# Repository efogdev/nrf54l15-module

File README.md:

## Codename "Chinchilla"

### ❗️ DO NOT BUILD ❗️
### ❗️ The design has a critical issue ❗️

## Features

1. Full IO set: all the GPIO and programming pins are present
2. Compact design: the board is 16.4x25.3 mm with ≈4.8 mm of total height
3. Ultra efficient: featuring TLV62569 with ≥92% efficiency at (almost) any load
4. 1V8 pin can be used as both input (if VIN not connected) and output (up to 1.5A)
5. 4 programmable LEDs (200 µA) that can be isolated to free the pins
6. On-board "reset" switch and an additional general purpose button (High/High-Z)
7. Impedance of (almost) all traces is close to 50Ω
8. Board-to-board connector with programming, power and GPIO pins 

## Stackup

JLC06121H-3313

## Dimensions

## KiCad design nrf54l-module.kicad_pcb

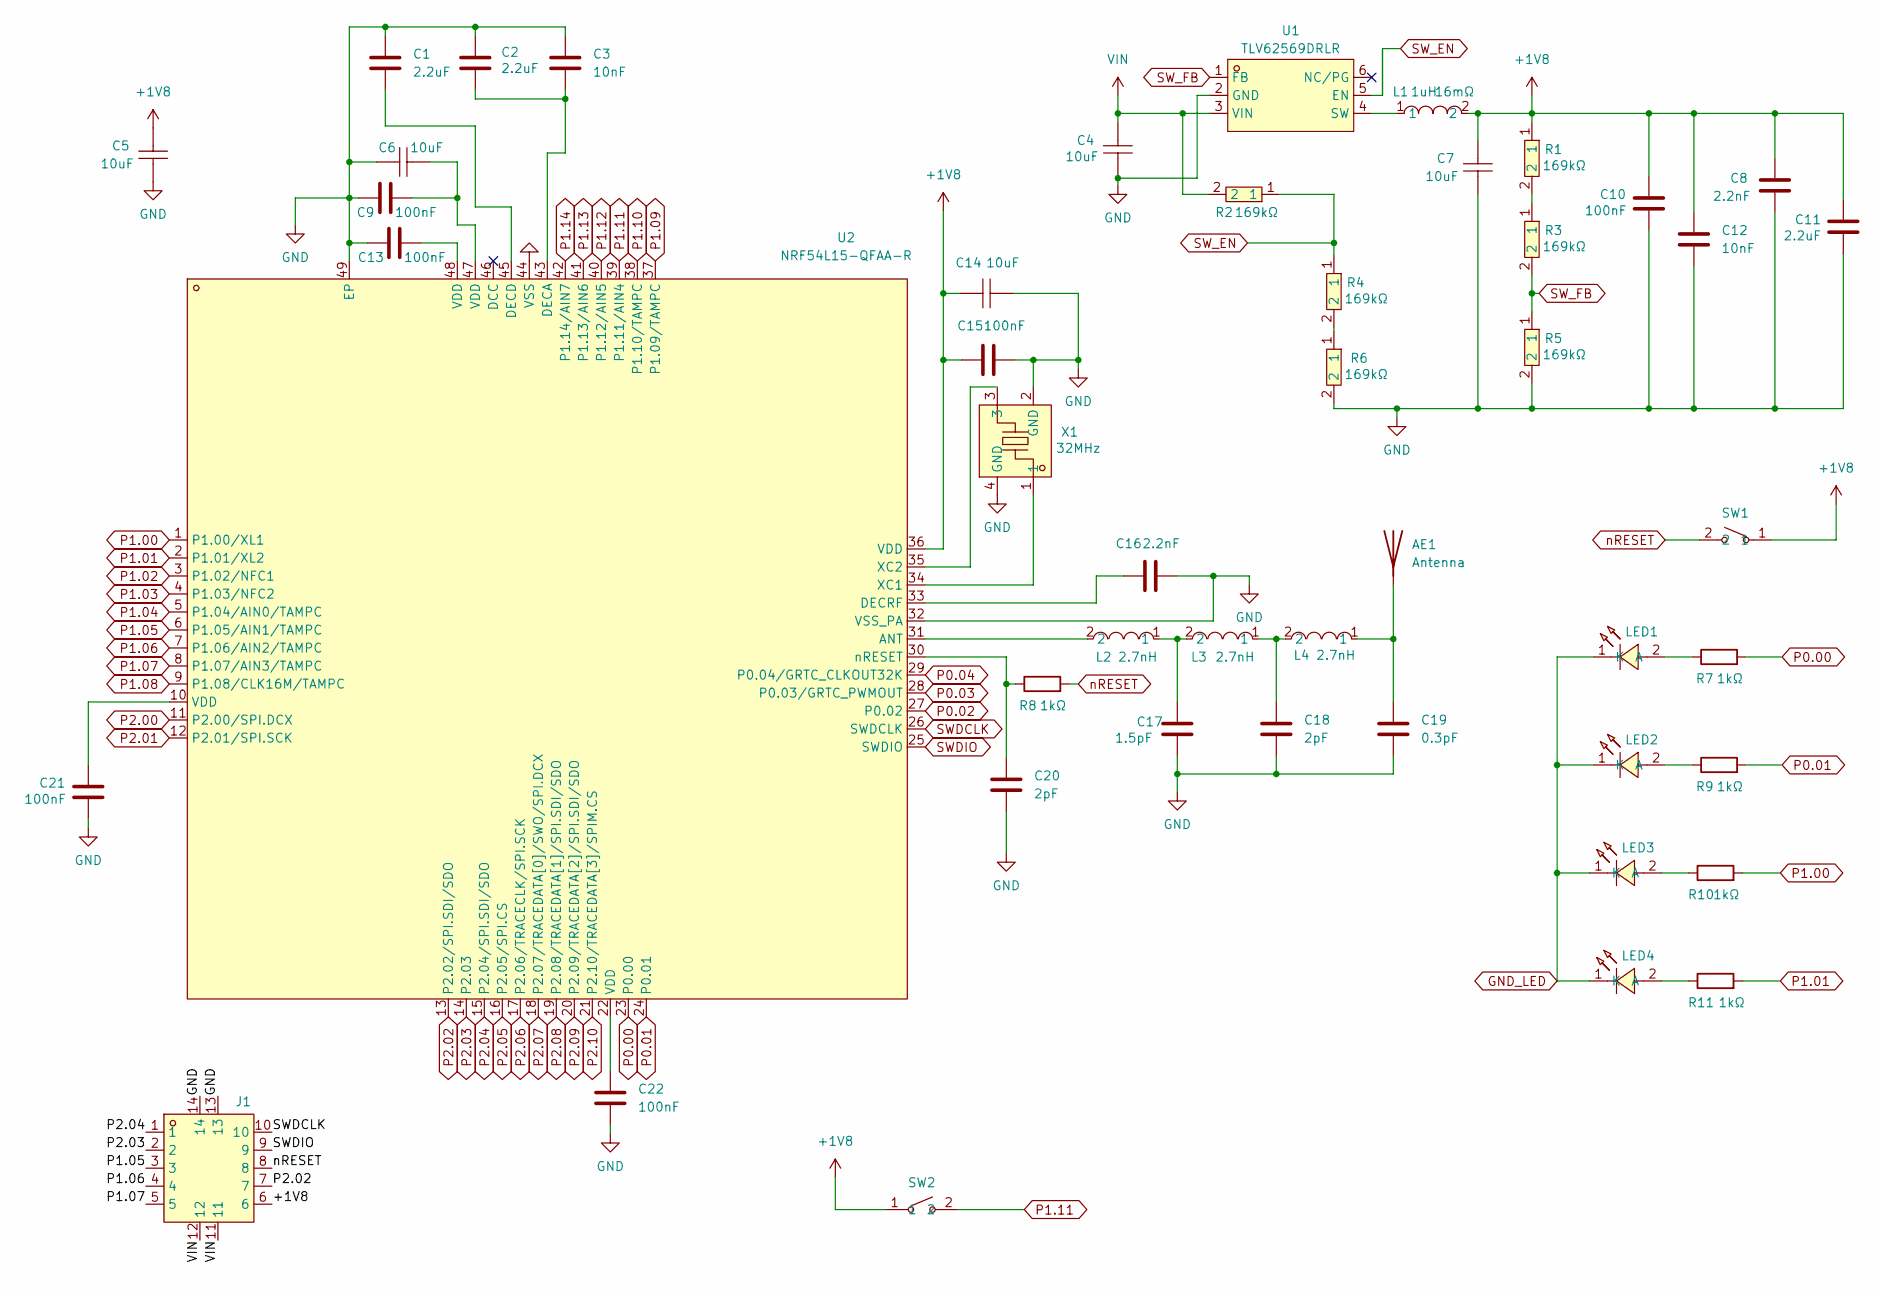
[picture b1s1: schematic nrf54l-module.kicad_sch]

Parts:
AE1: Antenna; Texas_SWRA117D_2.4GHz_Left
C1, C2, C11: 2.2uF; C_0201_0603Metric; LCSC Part C76933
C3, C12: 10nF; C_0201_0603Metric; LCSC Part C76941
C4, C5, C6, C7, C14: 10uF; C0402; LCSC Part C76991
C8, C16: 2.2nF; C_0201_0603Metric; LCSC Part C97860
C9, C10, C13, C15, C21, C22: 100nF; C_0201_0603Metric; LCSC Part C668346
C17: 1.5pF; C_0201_0603Metric; LCSC Part C88913
C18, C20: 2pF; C_0201_0603Metric; LCSC Part C426046
C19: 0.3pF; C_0201_0603Metric; LCSC Part C76927
J1: BM28B0.6-10DS/2-0.35V(51); CONN-SMD_BM28B0.6-10DS-2-0.35V-51; LCSC Part C424563
L1: 1uH; L1008; LCSC Part C22400405
L2, L3, L4: MLG0603P2N7CT000; L0201; LCSC Part C76752
LED1, LED2, LED3, LED4: TZ-P2-0402RTIA1-0.45T; LED0402-RD_RED; LCSC Part C779449
R1, R2, R3, R4, R5, R6: RC0402FR-07160KL; R_0201_0603Metric; LCSC Part C166333
R7, R8, R9, R10, R11: 1kΩ; R_0201_0603Metric; LCSC Part C270365
SW1, SW2: KEY-SMD_B3U-1000PM; LCSC Part C231329
U1: TLV62569DRLR; SOT-563_L1.6-W1.2-P0.50-LS1.6-BL; LCSC Part C163217
U2: NRF54L15-QFAA-R; QFN-48_L6.0-W6.0-P0.40-TL-EP4.6; LCSC Part C42458750
X1: XL7EL89CKI-111YLC-32M; CRYSTAL-SMD_4P-L2.0-W1.6-BL; LCSC Part C2965582

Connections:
+1V8: C5.1, C7.1, C8.2, C10.2, C11.2, C12.1, C14.1, C15.1, J1.6, L1.2, R1.1, SW1.1, SW2.1, U2.36 (VDD)
GND: AE1.2, C1.1, C2.1, C3.1, C4.1, C5.2, C6.1, C7.2, C8.1, C9.1, C10.1, C11.1, C12.2, C13.2, C14.2, C15.2, C16.2, C17.2, C18.2, C19.2, C20.2, C21.1, C22.2, J1.13, J1.14, R5.2, R6.2, U1.2 (GND), U2.32 (VSS_PA), U2.44 (VSS), U2.49 (EP), X1.2 (GND), X1.4 (GND)
GND_LED: LED1.1 (K), LED2.1 (K), LED3.1 (K), LED4.1 (K)
unnamed: AE1.1 (A), C19.1, L4.1
unnamed: C6.2, C9.2, U2.47 (VDD)
unnamed: C13.1, U2.48 (VDD)
unnamed: C17.1, L2.1, L3.2
unnamed: C18.1, L3.1, L4.2
unnamed: C21.2, U2.10 (VDD)
unnamed: C22.1, U2.22 (VDD)
unnamed: LED1.2 (A), R7.1
unnamed: LED2.2 (A), R9.1
unnamed: LED3.2 (A), R10.1
unnamed: LED4.2 (A), R11.1
unnamed: R1.2, R3.1
unnamed: R4.2, R6.1
unnamed: L1.1, U1.4 (SW)
unnamed: L2.2, U2.31 (ANT)
unnamed: C2.2, C3.2, U2.43 (DECA)
unnamed: C1.2, U2.45 (DECD)
unnamed: C16.1, U2.33 (DECRF)
unnamed: U2.34 (XC1), X1.1
unnamed: U2.35 (XC2), X1.3
unnamed: C20.1, R8.1, U2.30 (nRESET)
P0.00: R7.2, U2.23 (P0.00)
P0.01: R9.2, U2.24 (P0.01)
P0.02: U2.27 (P0.02)
P0.03: U2.28 (P0.03/GRTC_PWMOUT)
P0.04: U2.29 (P0.04/GRTC_CLKOUT32K)
P1.00: R10.2, U2.1 (P1.00/XL1)
P1.01: R11.2, U2.2 (P1.01/XL2)
P1.02: U2.3 (P1.02/NFC1)
P1.03: U2.4 (P1.03/NFC2)
P1.04: U2.5 (P1.04/AIN0/TAMPC)
P1.05: J1.3, U2.6 (P1.05/AIN1/TAMPC)
P1.06: J1.4, U2.7 (P1.06/AIN2/TAMPC)
P1.07: J1.5, U2.8 (P1.07/AIN3/TAMPC)
P1.08: U2.9 (P1.08/CLK16M/TAMPC)
P1.09: U2.37 (P1.09/TAMPC)
P1.10: U2.38 (P1.10/TAMPC)
P1.11: SW2.2, U2.39 (P1.11/AIN4)
P1.12: U2.40 (P1.12/AIN5)
P1.13: U2.41 (P1.13/AIN6)
P1.14: U2.42 (P1.14/AIN7)
P2.00: U2.11 (P2.00/SPI.DCX)
P2.01: U2.12 (P2.01/SPI.SCK)
P2.02: J1.7, U2.13 (P2.02/SPI.SDI/SDO)
P2.03: J1.2, U2.14 (P2.03)
P2.04: J1.1, U2.15 (P2.04/SPI.SDI/SDO)
P2.05: U2.16 (P2.05/SPI.CS)
P2.06: U2.17 (P2.06/TRACECLK/SPI.SCK)
P2.07: U2.18 (P2.07/TRACEDATA[0]/SWO/SPI.DCX)
P2.08: U2.19 (P2.08/TRACEDATA[1]/SPI.SDI/SDO)
P2.09: U2.20 (P2.09/TRACEDATA[2]/SPI.SDI/SDO)
P2.10: U2.21 (P2.10/TRACEDATA[3]/SPIM.CS)
SWDCLK: J1.10, U2.26 (SWDCLK)
SWDIO: J1.9, U2.25 (SWDIO)
SW_EN: R2.1, R4.1, U1.5 (EN)
SW_FB: R3.2, R5.1, U1.1 (FB)
VIN: C4.2, J1.11, J1.12, R2.2, U1.3 (VIN)
nRESET: J1.8, R8.2, SW1.2

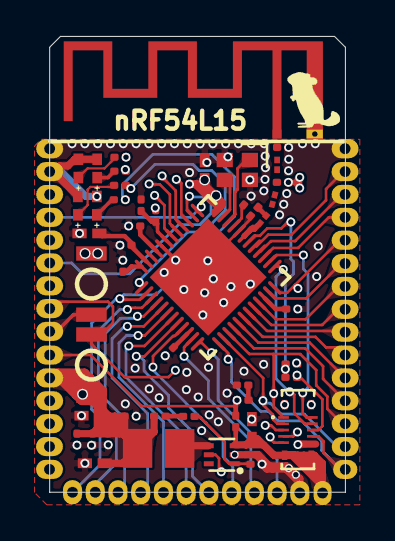
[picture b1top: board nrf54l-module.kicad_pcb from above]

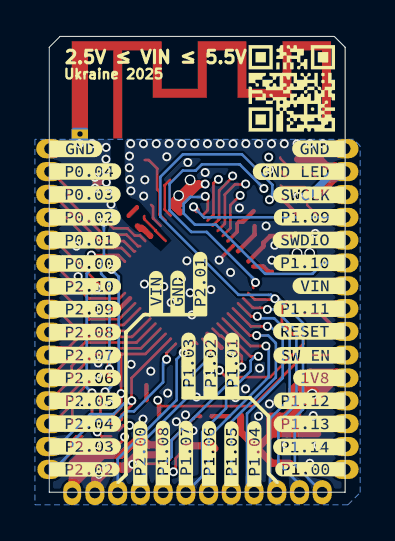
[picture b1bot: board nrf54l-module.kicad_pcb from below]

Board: 6 copper layers, 16.4 x 25.3 mm, 90 parts (42 on the bottom side), 41 nets.

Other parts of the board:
kibuzzard-684F74F9: G***; kibuzzard-684F74F9
kibuzzard-684F75DA: G***; kibuzzard-684F75DA
kibuzzard-684F75DE: G***; kibuzzard-684F75DE
kibuzzard-684F75E1: G***; kibuzzard-684F75E1
kibuzzard-684F75E4: G***; kibuzzard-684F75E4
kibuzzard-684F75E9: G***; kibuzzard-684F75E9
kibuzzard-684F75ED: G***; kibuzzard-684F75ED
kibuzzard-684F75F1: G***; kibuzzard-684F75F1
kibuzzard-684F75F7: G***; kibuzzard-684F75F7
kibuzzard-684F75FF: G***; kibuzzard-684F75FF
kibuzzard-684F750C: G***; kibuzzard-684F750C
kibuzzard-684F751D: G***; kibuzzard-684F751D
kibuzzard-684F753F: G***; kibuzzard-684F753F
kibuzzard-684F761F: G***; kibuzzard-684F761F
kibuzzard-684F7560: G***; kibuzzard-684F7560
kibuzzard-684F7579: G***; kibuzzard-684F7579
kibuzzard-684F7581: G***; kibuzzard-684F7581
kibuzzard-684F7617: G***; kibuzzard-684F7617
kibuzzard-68448D45: G***; kibuzzard-68448D45
kibuzzard-68448D82: G***; kibuzzard-68448D82
kibuzzard-68448D96: G***; kibuzzard-68448D96
kibuzzard-68448DA6: G***; kibuzzard-68448DA6
kibuzzard-68463A68: G***; kibuzzard-68463A68
kibuzzard-68478D5A: G***; kibuzzard-68478D5A
kibuzzard-68478D5E: G***; kibuzzard-68478D5E
kibuzzard-68478D8D: G***; kibuzzard-68478D8D
kibuzzard-68478D9B: G***; kibuzzard-68478D9B
kibuzzard-68478D71: G***; kibuzzard-68478D71
kibuzzard-68478D86: G***; kibuzzard-68478D86
kibuzzard-68478D98: G***; kibuzzard-68478D98
kibuzzard-684623CD: G***; kibuzzard-684623CD
kibuzzard-6844924F: G***; kibuzzard-6844924F
kibuzzard-6844930A: G***; kibuzzard-6844930A
kibuzzard-6844930F: G***; kibuzzard-6844930F
kibuzzard-6844931D: G***; kibuzzard-6844931D
kibuzzard-68449253: G***; kibuzzard-68449253
kibuzzard-68449303: G***; kibuzzard-68449303
kibuzzard-68449307: G***; kibuzzard-68449307
kibuzzard-68449316: G***; kibuzzard-68449316
kibuzzard-68449351: G***; kibuzzard-68449351
kibuzzard-68449359: G***; kibuzzard-68449359
kibuzzard-68449360: G***; kibuzzard-68449360

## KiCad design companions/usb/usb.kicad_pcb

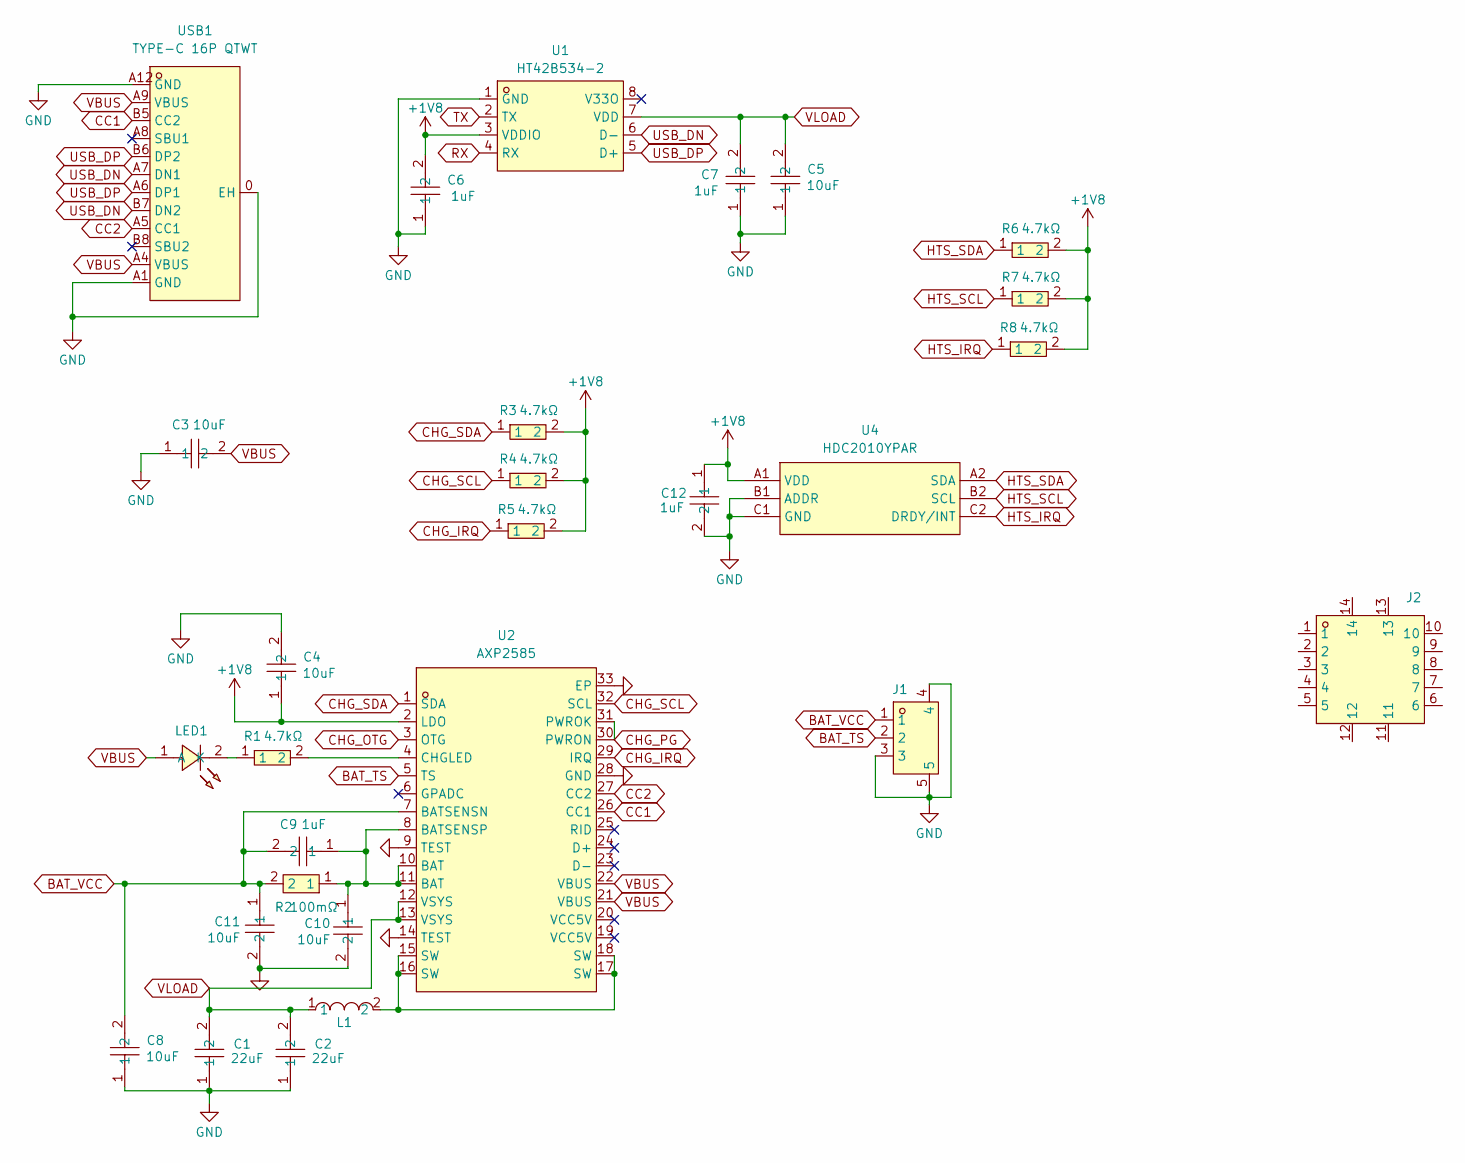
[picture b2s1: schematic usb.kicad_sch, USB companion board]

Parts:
C1, C2: GRM155R60J226ME11D; C0402; LCSC Part C415703
C3, C4, C5, C8, C10, C11: CL05A106MP5NUNC_C315248; C0402; LCSC Part C315248
C6, C7, C9, C12: CL03A105MQ3CSNH; C_0201_0603Metric; LCSC Part C53067
J1: HC-1.0-3PWT; CONN-SMD_3P-P1.0-HC-1.0-3PWT; LCSC Part C2845362
J2: BM28B0.6-10DP/2-0.35V(51); CONN-SMD_BM28B0.6-10DP-2-0.35V-51; LCSC Part C424562
L1: FTC252012S1R0MBCD; L1008; LCSC Part C22400405
LED1: XL-0201SURC; LED-SMD_L0.65-W0.35-P0.41_XL-0201SURC; LCSC Part C3646923
R1, R3, R4, R5, R6, R7, R8: CRCW02014K70FKED; R_0201_0603Metric; LCSC Part C3000902
R2: FRM121WFR100TM; R1206; LCSC Part C7467250
U1: HT42B534-2; SOP-8_L4.9-W3.9-P1.27-LS6.0-BL; LCSC Part C493294
U2: AXP2585; QFN-32_L5.0-W5.0-P0.40-TL-EP2.9; LCSC Part C20199912
U4: HDC2010YPAR; DSBGA-6_L1.5-W1.5-P0.50-BL; LCSC Part C477922
USB1: TYPE-C 16P QTWT; USB-TYPE-C-SMD_TYPE-C-16P-QTWT; LCSC Part C5187472

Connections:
+1V8: C4.1, C6.2, C12.1, R3.2, R4.2, R5.2, R6.2, R7.2, R8.2, U1.3 (VDDIO), U2.2 (LDO), U4.A1 (VDD)
BAT_TS: J1.2, U2.5 (TS)
BAT_VCC: C8.2, C9.2, C11.1, J1.1, R2.2, U2.7 (BATSENSN)
CC1: U2.26 (CC1), USB1.B5 (CC2)
CC2: U2.27 (CC2), USB1.A5 (CC1)
CHG_IRQ: R5.1, U2.29 (IRQ)
CHG_OTG: U2.3 (OTG)
CHG_PG: U2.30 (PWRON), U2.31 (PWROK)
CHG_SCL: R4.1, U2.32 (SCL)
CHG_SDA: R3.1, U2.1 (SDA)
GND: C1.1, C2.1, C3.1, C4.2, C5.1, C6.1, C7.1, C8.1, C10.2, C11.2, C12.2, J1.3, J1.4, J1.5, U1.1 (GND), U2.9 (TEST), U2.14 (TEST), U2.28 (GND), U2.33 (EP), U4.B1 (ADDR), U4.C1 (GND), USB1.0 (EH), USB1.A1 (GND), USB1.A12 (GND)
HTS_IRQ: R8.1, U4.C2 (DRDY/INT)
HTS_SCL: R7.1, U4.B2 (SCL)
HTS_SDA: R6.1, U4.A2 (SDA)
unnamed: L1.2, U2.15 (SW), U2.16 (SW), U2.17 (SW), U2.18 (SW)
unnamed: LED1.2 (K), R1.1
unnamed: C9.1, C10.1, R2.1, U2.8 (BATSENSP), U2.10 (BAT), U2.11 (BAT)
unnamed: R1.2, U2.4 (CHGLED)
RX: U1.4 (RX)
TX: U1.2 (TX)
USB_DN: U1.6 (D-), USB1.A7 (DN1), USB1.B7 (DN2)
USB_DP: U1.5 (D+), USB1.A6 (DP1), USB1.B6 (DP2)
VBUS: C3.2, LED1.1 (A), U2.21 (VBUS), U2.22 (VBUS), USB1.A4 (VBUS), USB1.A9 (VBUS)
VLOAD: C1.2, C2.2, C5.2, C7.2, L1.1, U1.7 (VDD), U2.12 (VSYS), U2.13 (VSYS)

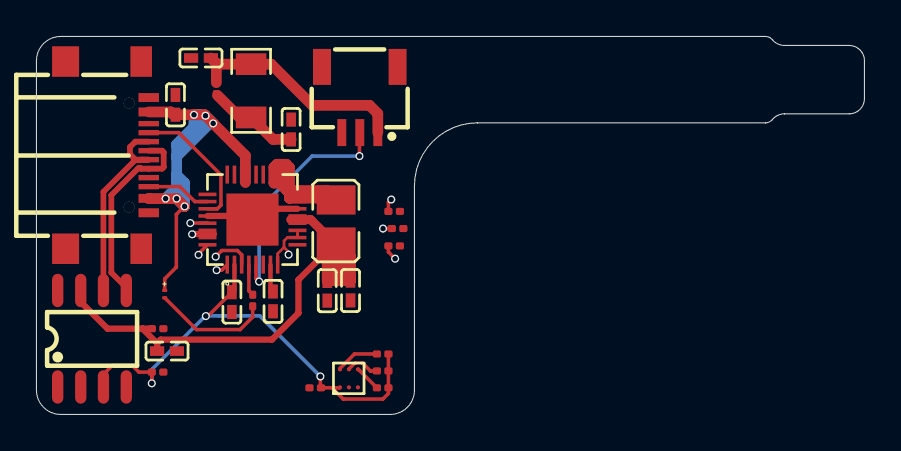
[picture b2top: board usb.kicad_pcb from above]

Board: 2 copper layers, 46.0 x 21.0 mm, 28 parts (1 on the bottom side), 21 nets.

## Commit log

2025-06-07 feat: initial commit
2025-06-07 chore: readme
2025-06-07 feat: back silkscreen
2025-06-07 bugfix: GND pad
2025-06-07 chore: refactoring
2025-06-07 bugfix: antenna design
2025-06-08 feat: chinchilla
2025-06-08 feat: images
2025-06-08 bugfix: DRC
2025-06-08 feat: dimensions
2025-06-08 feat: symbol and footprint
2025-06-08 feat: 1.27 mm pitch
2025-06-09 feat: updatd symbol and footprint
2025-06-09 feat: additinal button on P1.12
2025-06-09 feat: 6 layer because it's cheaper lol wtf
2025-06-14 chore: checkpoint
2025-06-16 feat: panel for github bug
2025-06-16 chore: images
2025-07-09 bugfix(critical): 1.8V power to VDD
